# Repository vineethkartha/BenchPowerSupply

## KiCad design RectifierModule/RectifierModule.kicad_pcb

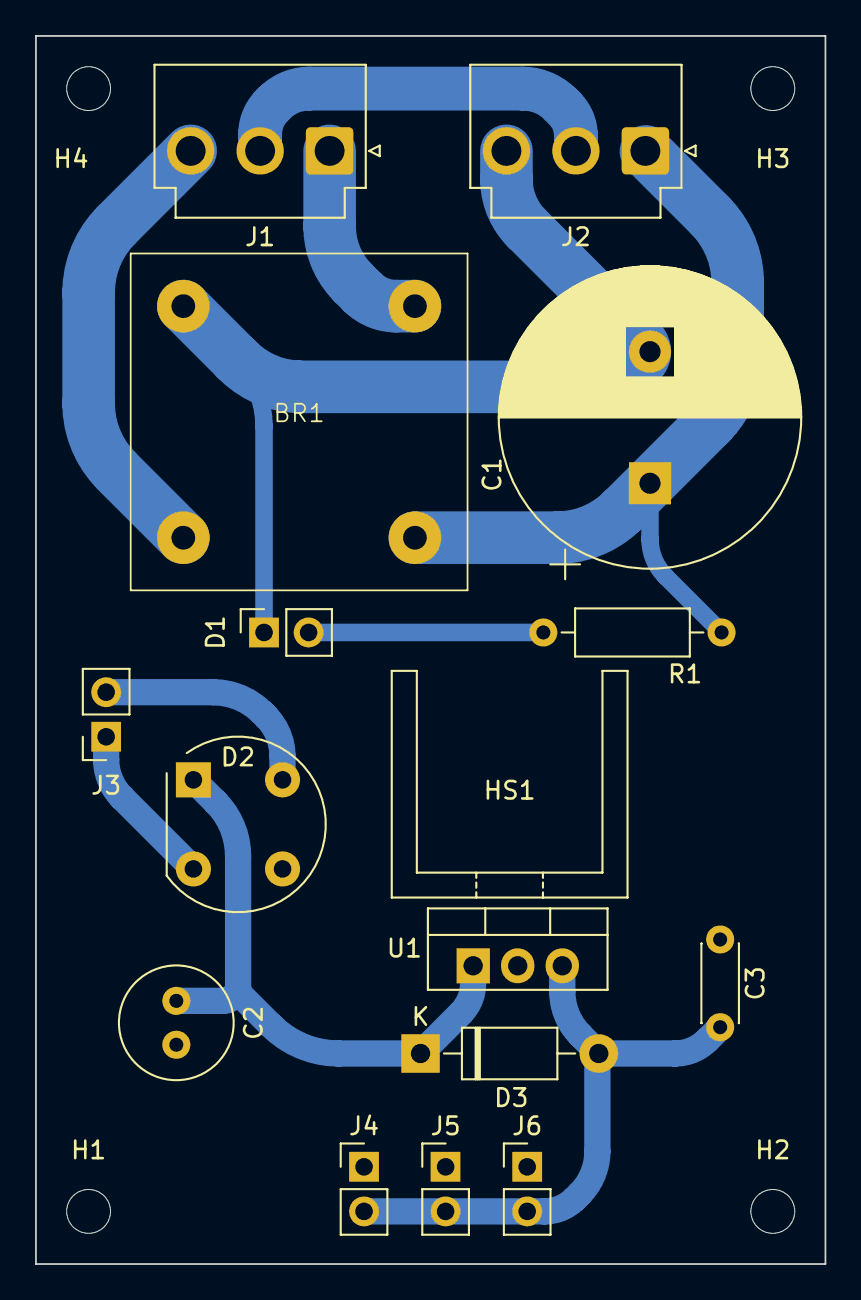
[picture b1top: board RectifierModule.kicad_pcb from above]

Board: 2 copper layers, 45.0 x 70.0 mm, 20 parts (0 on the bottom side), 11 nets.

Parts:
BR1: BRIDGE_RECTIFIER_CLASSIC; BR-10X
C1: 4700u; CP_Radial_D17.0mm_P7.50mm
C2: 100u; C_Radial_D6.3mm_H11.0mm_P2.50mm
C3: .1uF; C_Disc_D4.3mm_W1.9mm_P5.00mm
D1: LED; PinSocket_1x02_P2.54mm_Vertical
D2: W06G; Diode_Bridge_Round_D9.8mm
D3: 1N4007; D_DO-41_SOD81_P10.16mm_Horizontal
H1, H2, H3, H4: MountingHole; MountingHole_2.5mm
HS1: Heatsink; Heatsink_Stonecold_HS-S03_13.21x12.7mm
J1: TransformerIn; JST_VH_B3P-VH-B_1x03_P3.96mm_Vertical
J2: Rectified Out; JST_VH_B3P-VH-B_1x03_P3.96mm_Vertical
J3: AuxIn; PinSocket_1x02_P2.54mm_Vertical
J4: VA; PinHeader_1x02_P2.54mm_Vertical
J5: FAN; PinHeader_1x02_P2.54mm_Vertical
J6: Extra; PinHeader_1x02_P2.54mm_Vertical
R1: 220; R_Axial_DIN0207_L6.3mm_D2.5mm_P10.16mm_Horizontal
U1: LM7812_TO220; TO-220-3_Vertical

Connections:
/12V+: C2.1, D2.1 (+), D3.1 (K), U1.1 (VI)
/30V+: BR1.2, C1.1, J2.1, R1.1
/30V-: BR1.1, C1.2, D1.1 (K), J2.3
/AC_IN_L: BR1.4, J1.3
/AC_IN_N: BR1.3, J1.1
/Aux_input_L: D2.4, J3.2
/Aux_input_N: D2.2, J3.1
/Aux_out: C3.1, D3.2 (A), J4.2, J5.2, J6.2, U1.3 (VO)
/CentreTap: J1.2, J2.2
GND: C2.2, C3.2, D2.3 (-), J4.1, J5.1, J6.1, U1.2 (GND)
unnamed: D1.2 (A), R1.2

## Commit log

2023-12-17 Initial Submit
2023-12-17 Update gitignore to skip backup files
2023-12-17 Updates to the schematic to make use of the centre tapped transformer to get negative rail.
2023-12-19 Split the design into two separate KiCad projects. 1. The Main Rectifier board with auxilliary 12V supply 2. LM317 Variable Supply module
2023-12-19 Updated net lists in the schematic
    The schematic has all nets assigned to a net class. And the schematic has been tidied up
2023-12-19 Fixed all ERC warnings
    There were several ERC warning regarding mismatch in port types. These have been fixed by modifying the library symbols
2023-12-19 Updated footprints
    Updated foot prints of all the components in the list
2023-12-19 Generated PCB layout
    Some minor updates in the schematic and created the PCB layout for the rectifier module
2023-12-20 Updated the capacitor at input of 7812
2023-12-20 Add mounting holes and their footprints
2023-12-20 Added heat sink and made changes to accommodate the heatsink
2023-12-21 Curved tracks in pcb and BOM
